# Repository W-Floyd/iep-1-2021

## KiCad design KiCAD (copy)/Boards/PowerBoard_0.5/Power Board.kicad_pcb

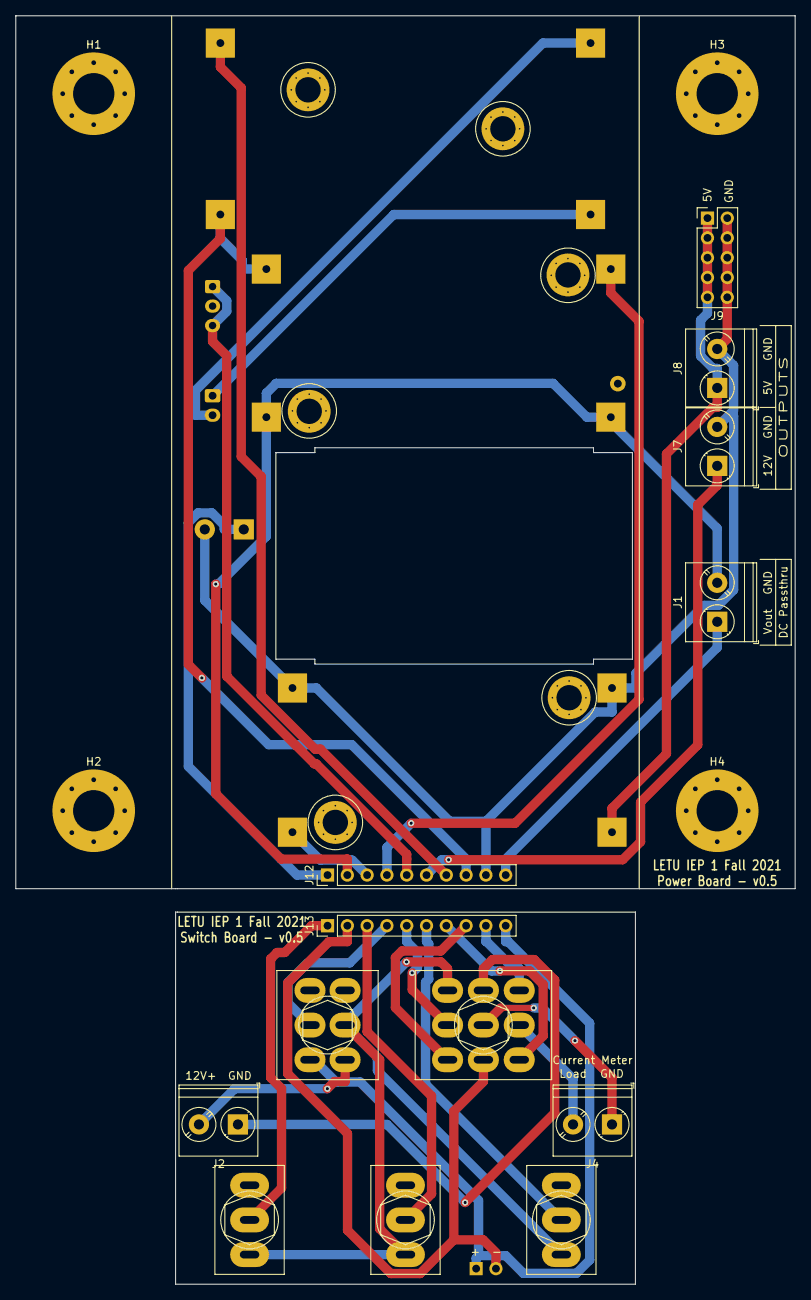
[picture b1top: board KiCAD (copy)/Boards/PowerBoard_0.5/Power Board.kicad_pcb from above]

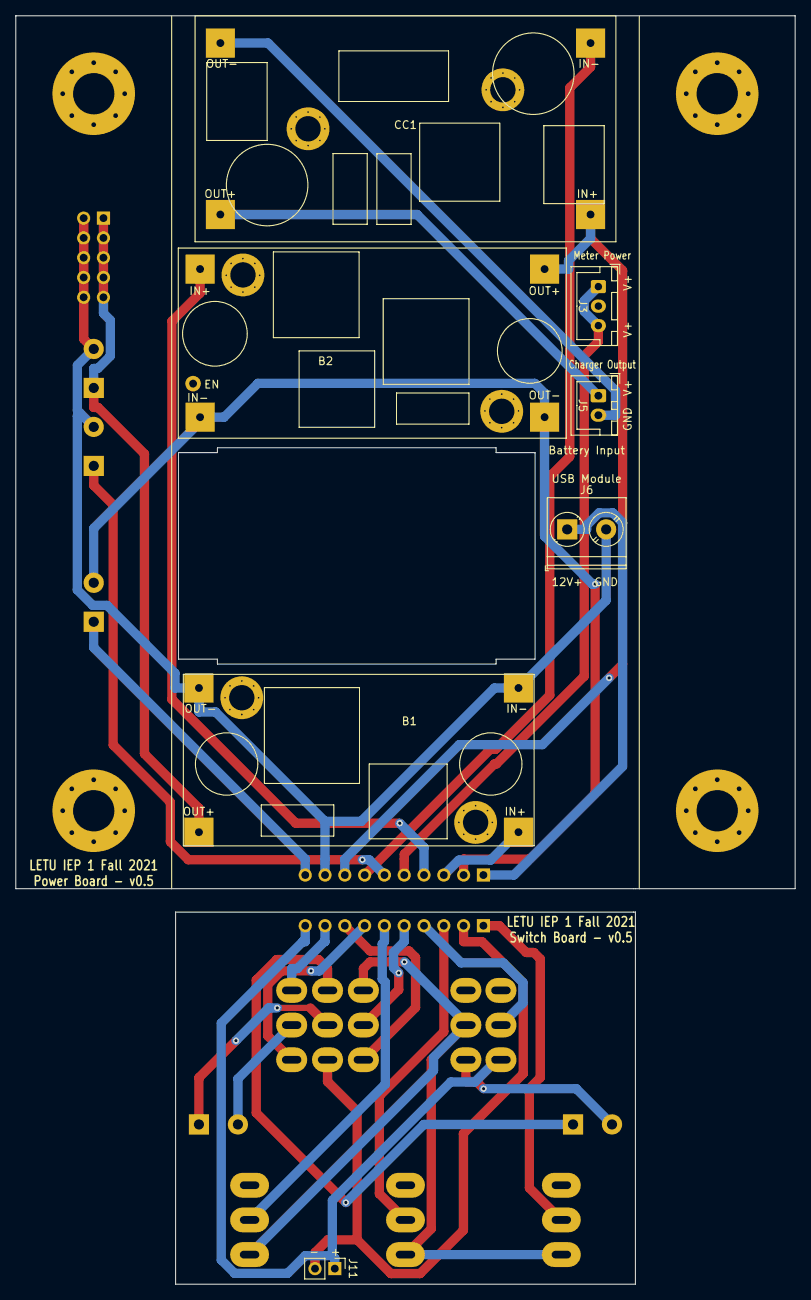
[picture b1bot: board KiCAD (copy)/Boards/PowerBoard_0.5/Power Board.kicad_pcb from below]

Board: 2 copper layers, 100.0 x 162.8 mm, 24 parts (7 on the bottom side), 28 nets.

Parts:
B1: BuckConverter
B2: BuckBoostConverter
CC1: CurrentLimiter; ConstantCurrentModule
H1, H2, H3, H4: MountingHole; MountingHole_5.3mm_M5_Pad_Via
J1, J2, J4, J6, J7, J8: Screw_Terminal_01x02; TerminalBlock_Phoenix_PT-1,5-2-5.0-H_1x02_P5.00mm_Horizontal
J3: Conn_01x03; JST_XH_B3B-XH-A_1x03_P2.50mm_Vertical
J5: Conn_01x02; JST_XH_B2B-XH-A_1x02_P2.50mm_Vertical
J9: Conn_02x05_Odd_Even; PinHeader_2x05_P2.54mm_Vertical
J11: Conn_01x02; PinHeader_1x02_P2.54mm_Vertical
J12, J13: Conn_01x10; PinHeader_1x10_P2.54mm_Vertical
SW1: SW_DPST; DPDT_OnOff
SW2: SW_3PDT_x3; 3PDT
SW3, SW4, SW5: SW_SPST; SPDT

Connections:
/Switches/5V_+: B1.1, J12.3
/Switches/12V_+: J7.1, J12.6
/Switches/15V_+: B2.3, CC1.1, J12.8
/Switches/CC_-: CC1.2, J12.7
/Switches/DC_+: B2.1, J12.4
/Switches/DC_-: B2.2, B2.4, J1.2, J12.2
/Switches/DC_RAW_+: J1.1, J12.10
/Switches/Meter_+: J3.1, J3.3, J12.5
/Switches/USB_+: J6.1, J12.1
Bridge_5V_+: J13.3, SW3.2
Bridge_12V_+: J13.6, SW5.2
Bridge_15V_+: J13.8, SW2.3
Bridge_BAT_+: SW1.2, SW2.1, SW3.1, SW4.1, SW5.1
Bridge_BAT_-: J2.1, SW2.4
Bridge_CC_-: J13.7, SW2.9
Bridge_DC_+: J13.4, SW1.4
Bridge_DC_-: J11.2, J13.2, SW2.6
Bridge_DC_RAW_+: J11.1, J13.10, SW1.3
Bridge_GND: J13.9, SW2.7
Bridge_Meter_+: J13.5, SW2.2
Bridge_USB_+: J13.1, SW4.2
GND: B1.2, B1.4, J6.2, J7.2, J8.2, J9.2, J9.4, J9.6, J9.8, J9.10, J12.9
unnamed: B1.3, J8.1, J9.1, J9.3, J9.5, J9.7, J9.9
unnamed: CC1.3, J5.1
unnamed: CC1.4, J5.2
unnamed: J2.2, SW1.1
unnamed: J4.1, SW2.5
unnamed: J4.2, SW2.8

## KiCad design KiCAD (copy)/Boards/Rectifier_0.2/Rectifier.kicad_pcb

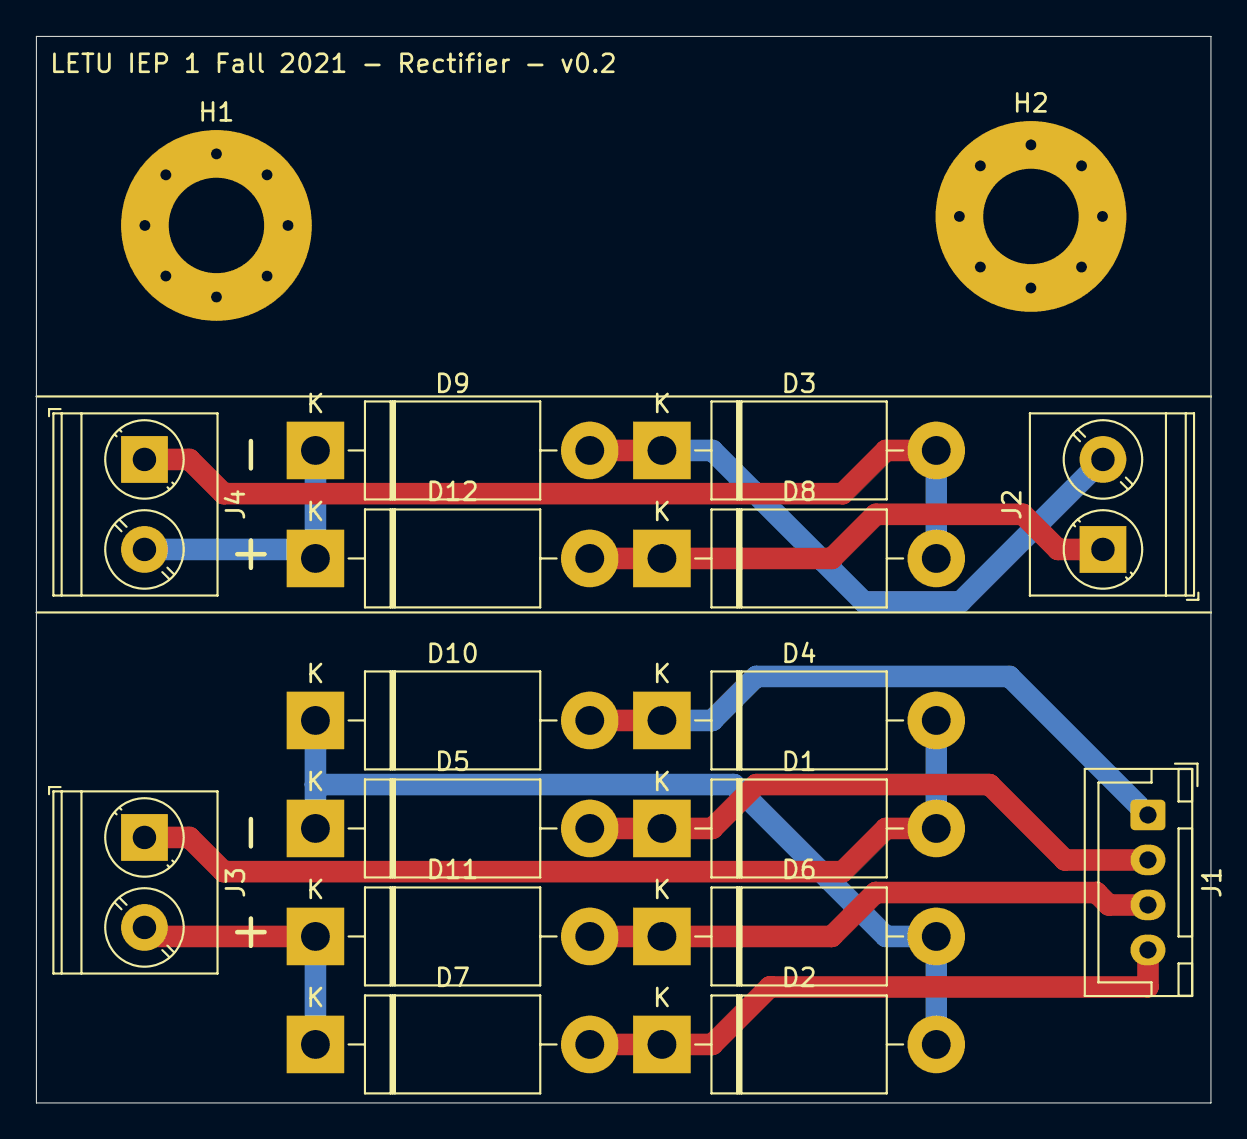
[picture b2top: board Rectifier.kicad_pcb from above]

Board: 2 copper layers, 65.2 x 59.2 mm, 18 parts (0 on the bottom side), 11 nets.

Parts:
D1, D2, D3, D4, D5, D6, D7, D8, D9, D10, D11, D12: 1N5400; D_DO-201AD_P15.24mm_Horizontal
H1, H2: MountingHole; MountingHole_5.3mm_M5_Pad_Via
J1: Conn_01x04; JST_XH_B4B-XH-A_1x04_P2.50mm_Vertical
J2, J3, J4: Screw_Terminal_01x02; TerminalBlock_Phoenix_PT-1,5-2-5.0-H_1x02_P5.00mm_Horizontal

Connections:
unnamed: D1.1, D5.2, J1.2
unnamed: D1.2, D4.2, J3.1
unnamed: D2.1, D7.2, J1.4
unnamed: D3.1, D9.2, J2.2
unnamed: D3.2, D8.2, J4.1
unnamed: D2.2, D5.1, D6.2, D10.1
unnamed: D4.1, D10.2, J1.1
unnamed: D7.1, D11.1, J3.2
unnamed: D6.1, D11.2, J1.3
unnamed: D9.1, D12.1, J4.2
unnamed: D8.1, D12.2, J2.1

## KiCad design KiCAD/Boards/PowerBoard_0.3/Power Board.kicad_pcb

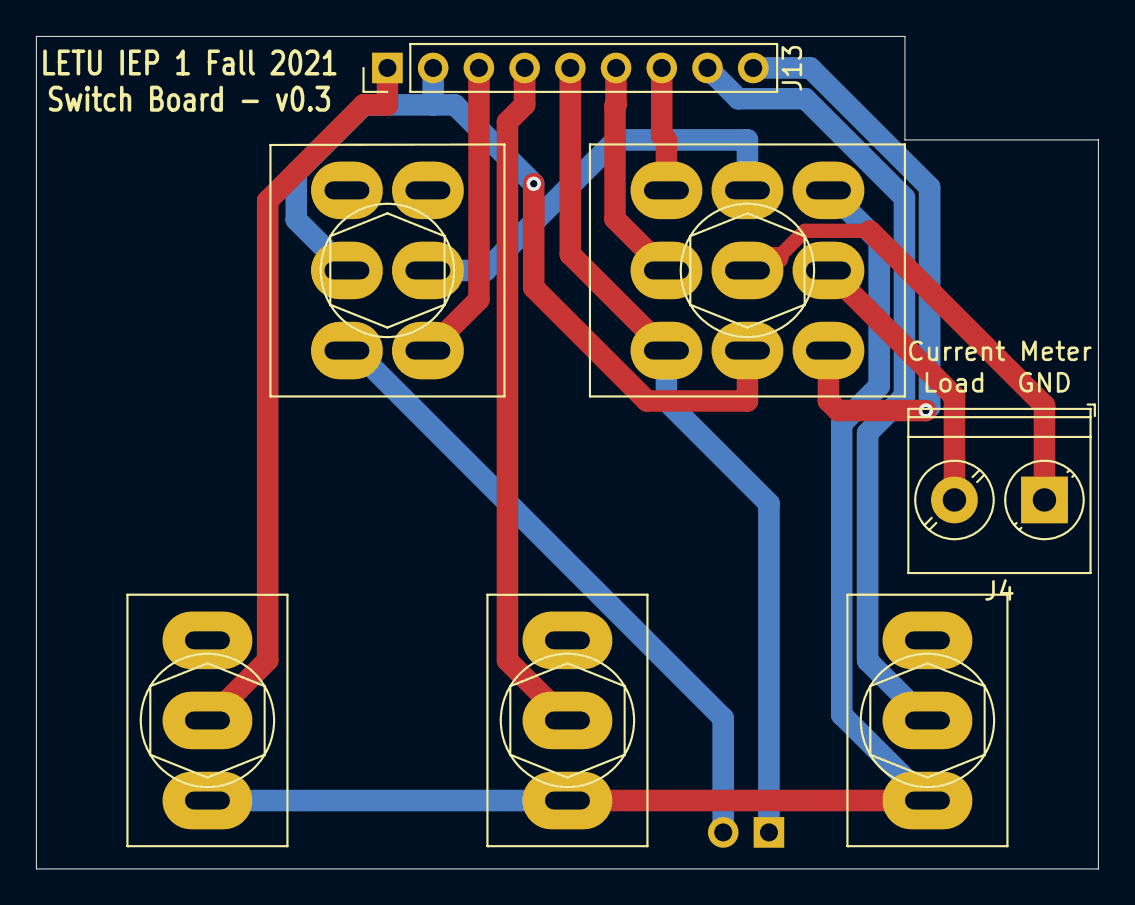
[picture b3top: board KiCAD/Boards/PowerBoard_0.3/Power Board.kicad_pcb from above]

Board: 2 copper layers, 59.0 x 46.2 mm, 8 parts (1 on the bottom side), 14 nets.

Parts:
J4: Screw_Terminal_01x02; TerminalBlock_Phoenix_PT-1,5-2-5.0-H_1x02_P5.00mm_Horizontal
J11: Conn_01x02; PinHeader_1x02_P2.54mm_Vertical
J13: Conn_01x09; PinHeader_1x09_P2.54mm_Vertical
SW1: SW_DPST; DPDT_OnOff
SW2: SW_3PDT_x3; 3PDT
SW3, SW4, SW5: SW_SPST; SPDT

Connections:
Bridge_5v_-: J13.4, SW3.2
Bridge_12V_-: J13.8, SW5.2
Bridge_BAT_+: J13.7, SW2.1
Bridge_BAT_-: J13.3, SW1.1
Bridge_CC_-: J13.9, SW2.9
Bridge_DC_+: J11.1, J13.5, SW2.3
Bridge_DC_-: J13.2, SW1.4, SW2.6
Bridge_Meter_+: J13.6, SW2.2
Bridge_USB_-: J13.1, SW4.2
unnamed: J4.1, SW2.5
unnamed: J4.2, SW2.8
unnamed: J11.2, SW1.3
unnamed: SW1.2, SW2.4
unnamed: SW2.7, SW3.1, SW4.1, SW5.1

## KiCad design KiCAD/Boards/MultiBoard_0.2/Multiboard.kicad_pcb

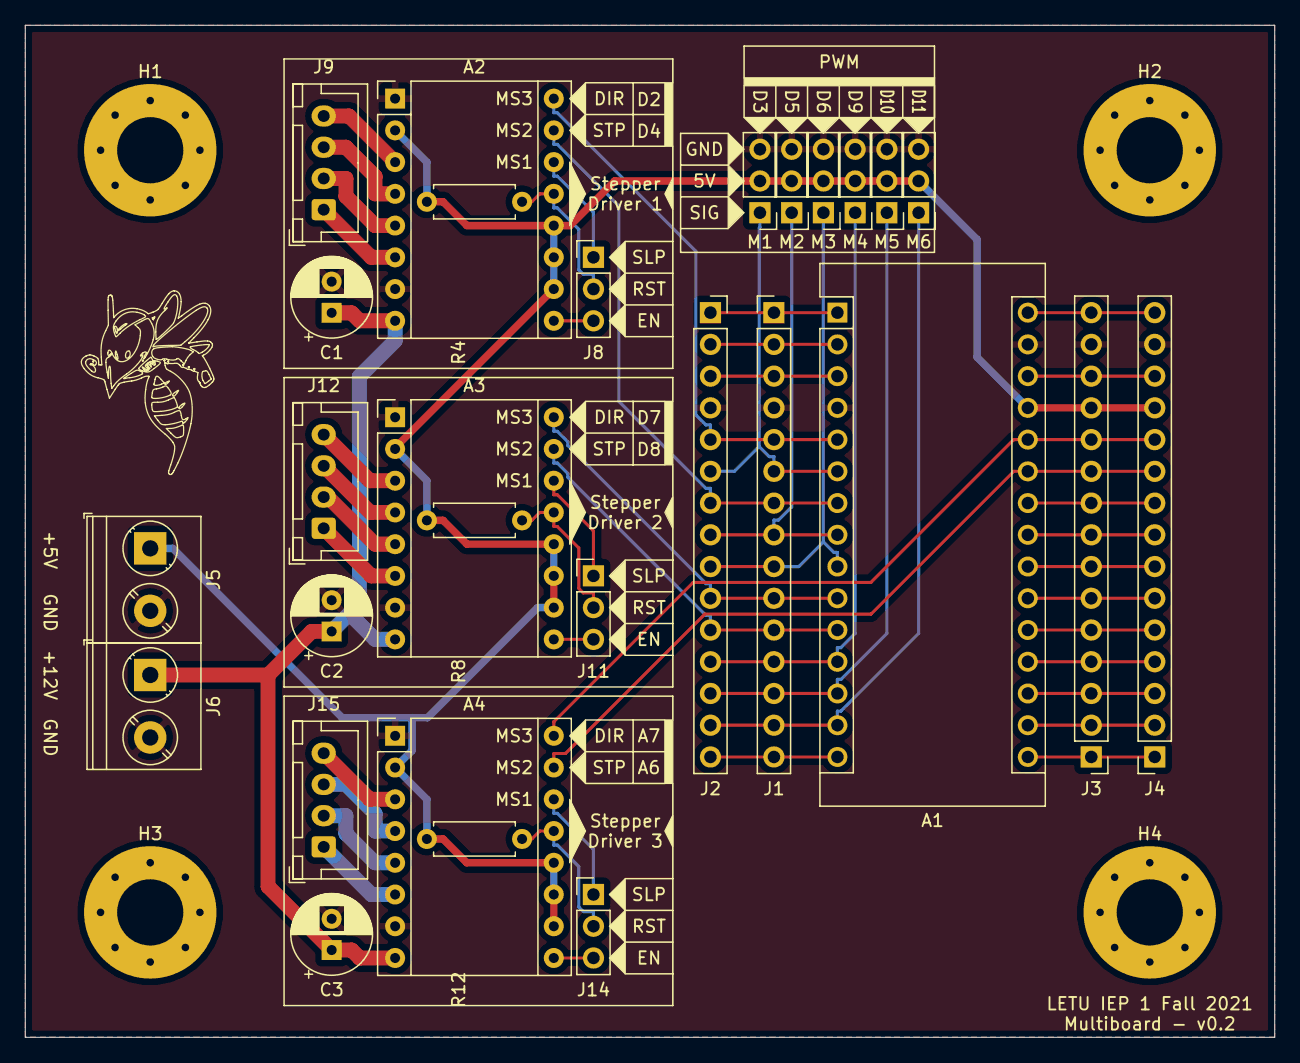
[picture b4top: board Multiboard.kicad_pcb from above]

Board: 2 copper layers, 100.0 x 81.0 mm, 32 parts (0 on the bottom side), 51 nets.

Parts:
A1: Arduino_Nano_v3.x; Arduino_Nano
A2, A3, A4: Pololu_Breakout_A4988; Pololu_Breakout-16_15.2x20.3mm
C1, C2, C3: 100uF; CP_Radial_D6.3mm_P2.50mm
H1, H2, H3, H4: MountingHole; MountingHole_5.3mm_M5_Pad_Via
J1, J3: Conn_01x15; PinHeader_1x15_P2.54mm_Vertical
J2, J4: Conn_01x15; PinSocket_1x15_P2.54mm_Vertical
J5, J6: Screw_Terminal_01x02; TerminalBlock_Phoenix_PT-1,5-2-5.0-H_1x02_P5.00mm_Horizontal
J8, J11, J14: Conn_01x03; PinHeader_1x03_P2.54mm_Vertical
J9, J12, J15: Conn_01x04; JST_XH_B4B-XH-A_1x04_P2.50mm_Vertical
M1, M2, M3, M4, M5, M6: Motor_Servo; PinHeader_1x03_P2.54mm_Vertical
R4, R8, R12: 10K; R_Axial_DIN0207_L6.3mm_D2.5mm_P7.62mm_Horizontal

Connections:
+5V: A1.27, A2.2, A2.10, A2.11, A2.12, A3.2, A3.10, A3.11, A3.12, A4.2, A4.10, A4.11, A4.12, J3.12, J4.12, J5.1, M1.2, M2.2, M3.2, M4.2, M5.2, M6.2, R4.2, R8.2, R12.2
+12V: A2.8, A3.8, A4.8, C1.1, C2.1, C3.1, J6.1
/Stepper/DIR: A1.5, A2.16, J1.5, J2.5
/Stepper/STEP: A1.7, A2.15, J1.7, J2.7
/sheet60A7C39C/DIR: A1.26, A4.16, J3.11, J4.11
/sheet60A7C39C/STEP: A1.25, A4.15, J3.10, J4.10
/sheet610CB91D/DIR: A1.10, A3.16, J1.10, J2.10
/sheet610CB91D/STEP: A1.11, A3.15, J1.11, J2.11
GND: A1.4, A1.29, A2.1, A2.7, A3.1, A3.7, A4.1, A4.7, C1.2, C2.2, C3.2, J1.4, J2.4, J3.14, J4.14, J5.2, J6.2, M1.3, M2.3, M3.3, M4.3, M5.3, M6.3
unnamed: A1.1, J1.1, J2.1
unnamed: A1.2, J1.2, J2.2
unnamed: A1.3, J1.3, J2.3
unnamed: A1.6, J1.6, J2.6, M1.1
unnamed: A1.8, J1.8, J2.8, M2.1
unnamed: A1.9, J1.9, J2.9, M3.1
unnamed: A1.12, J1.12, J2.12, M4.1
unnamed: A1.13, J1.13, J2.13, M5.1
unnamed: A1.14, J1.14, J2.14, M6.1
unnamed: A1.15, J1.15, J2.15
unnamed: A1.16, J3.1, J4.1
unnamed: A1.17, J3.2, J4.2
unnamed: A1.18, J3.3, J4.3
unnamed: A1.19, J3.4, J4.4
unnamed: A1.20, J3.5, J4.5
unnamed: A1.21, J3.6, J4.6
unnamed: A1.22, J3.7, J4.7
unnamed: A1.23, J3.8, J4.8
unnamed: A1.24, J3.9, J4.9
unnamed: A1.28, J3.13, J4.13
unnamed: A1.30, J3.15, J4.15
unnamed: A2.3, J9.4
unnamed: A2.4, J9.3
unnamed: A2.5, J9.2
unnamed: A2.6, J9.1
unnamed: A2.9, J8.3
unnamed: A2.13, J8.2, R4.1
unnamed: A2.14, J8.1
unnamed: A3.3, J12.4
unnamed: A3.4, J12.3
unnamed: A3.5, J12.2
unnamed: A3.6, J12.1
unnamed: A3.9, J11.3
unnamed: A3.13, J11.2, R8.1
unnamed: A3.14, J11.1
unnamed: A4.3, J15.4
unnamed: A4.4, J15.3
unnamed: A4.5, J15.2
unnamed: A4.6, J15.1
unnamed: A4.9, J14.3
unnamed: A4.13, J14.2, R12.1
unnamed: A4.14, J14.1

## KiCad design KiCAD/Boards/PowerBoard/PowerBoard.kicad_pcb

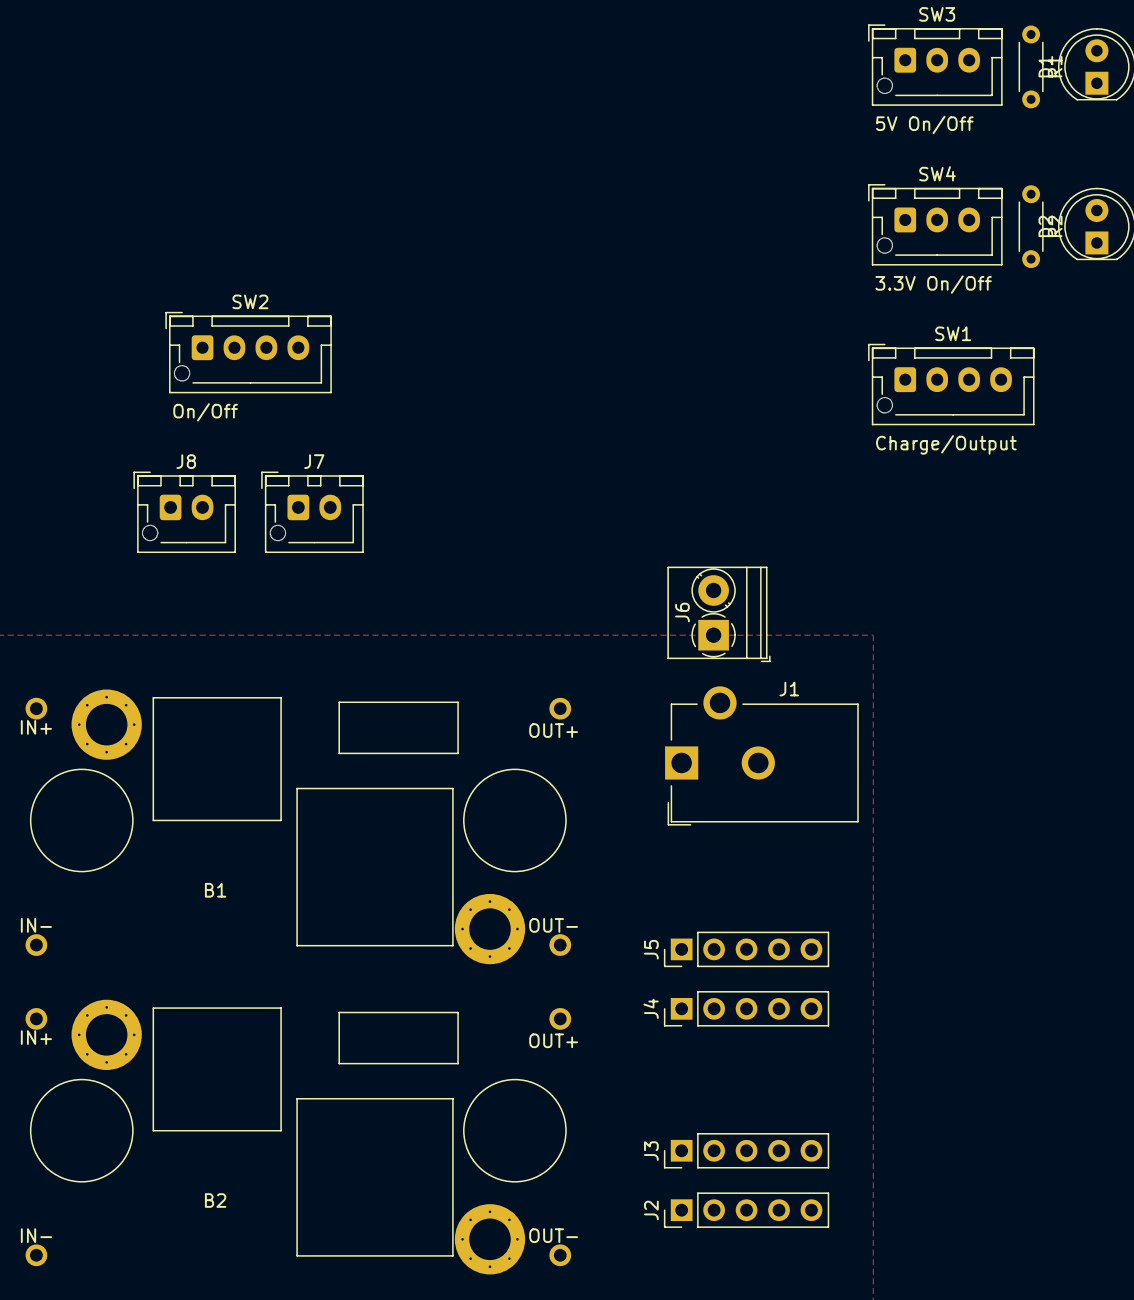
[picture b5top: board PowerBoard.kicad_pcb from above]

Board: 2 copper layers, 18 parts (0 on the bottom side), 12 nets, no tracks yet.

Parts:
B1, B2: BuckConverter; BuckConverterSmall
D1, D2: LED; LED_D5.0mm
J1: Conn_01x02_Female; BarrelJack_CUI_PJ-102AH_Horizontal
J2, J3, J4, J5: Conn_01x05_Male; PinHeader_1x05_P2.54mm_Vertical
J6: Conn_01x02_Female; TerminalBlock_2Pin_3.5mm_Amazon
J7, J8: Conn_01x02_Male; JST_XH_B2B-XH-AM_1x02_P2.50mm_Vertical
R1: R150; R_Axial_DIN0204_L3.6mm_D1.6mm_P5.08mm_Horizontal
R2: R65; R_Axial_DIN0204_L3.6mm_D1.6mm_P5.08mm_Horizontal
SW1, SW2: SW_DPST; JST_XH_B4B-XH-AM_1x04_P2.50mm_Vertical
SW3, SW4: SW_SPDT; JST_XH_B3B-XH-AM_1x03_P2.50mm_Vertical

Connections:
+3V3: B2.3, J5.1, J5.2, J5.3, J5.4, J5.5, R2.2
+5V: B1.3, J3.1, J3.2, J3.3, J3.4, J3.5, R1.2
+BATT: J7.1, SW1.1
+VDC: J1.1, J6.1, SW1.3
/Buck3V3/VoltageIn: B2.1, SW4.1
/Buck5V/VoltageIn: B1.1, SW3.1
GND: B1.2, B1.4, B2.2, B2.4, D1.1, D2.1, J1.2, J2.1, J2.2, J2.3, J2.4, J2.5, J4.1, J4.2, J4.3, J4.4, J4.5, J6.2, J7.2, J8.2
unnamed: D1.2, R1.1
unnamed: D2.2, R2.1
unnamed: SW1.2, SW2.1
unnamed: SW1.4, SW2.3
unnamed: SW2.2, SW3.2, SW4.2

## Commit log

2021-03-20 lib: Add custom library.
2021-03-26 all: Add.
2021-05-11 misc
2022-01-28 all: Add various parts.
2022-01-28 all: Add much work.
2022-01-28 Power board; Add 0.5
2022-01-28 all: More work.
2022-01-28 kicad: Add 0.4 power board.
2022-01-28 all: Dump of files from last summer.
